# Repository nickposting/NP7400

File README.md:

# NP7400  

## Processor Card

### Docs
[g4pinout.pdf](/docs/g4pinout.pdf) contains the pinout of the connector used on
Power Mac G4 computers. Some important notes regarding the pinout:

* Pin assignments were determined by first sanding/filing down the processor
card (8 layers) from a 667MHz Digital Audio G4, and then using the card from
a 400MHz AGP Graphics G4, intact, albeit with the processor desoldered,
to verify that all the connections were correct.
* None of the cards involved in this process were dual-processor cards, so any
assignments unique to dual-processor systems, if any exist, have not been 
recorded.
* As written, the pin assignments are representative of how an MPC7450-series
MPU would be interfaced to the Power Mac motherboard -- for instance, only address
bits A4-A35 are present on the connector. Unlike earlier G4 processors, the 7450
features an extended 36-bit address bus, however, the four most significant bits
(A0-A3) are not used in Power Mac systems. Bearing in mind that PowerPC datasheet
conventions specify bit zero as the most-significant bit, a processor card design
featuring an earlier 7400/7410 MPU with a 32-bit address bus would need to have the
MPU's bit A31 connected to the pin labelled "A35" on the pinout, A30 connected to
"A34," and so on. The same applies to the DTI (Data Transaction Index) signals, of
which there are less on MPUs predating the 7450.

Regarding pins marked "special":
* Pins marked "R" are connected only to resistor straps, most of which go to ground.
I am still trying to understand the purpose of most of these. Some straps are
unpopulated on every board in my possession, whereas others vary between boards.
* SDA and SCL are connected only to the SPD I<sup>2</sup>C EEPROM on every board.
* Pins B2 and K30 are connected only to each other on every board. I assume this is
intended for the motherboard to sense whether or not the processor card is fully
seated.
* CKSTP# on the connector is directly connected to both CKSTP_IN# and CKSTP_OUT# on
the MPU.
* D63 is pulled to ground by a 1kΩ resistor on every board for some reason.
* The length of the SYSCLK track in particular is critical (tangentially, it appears
that on cards built for Power Macs with a 167MHz FSB, most track lengths become
tightly controlled).

## VRM

### Docs
[820-1152-A.pdf](/docs/820-1152-A.pdf) contains a poor schematic of the
original VRM board in the Power Mac G4 Cube, drawn only to verify whether or not
there was anything "unusual" about the OEM design (for all intents and purposes,
there isn't).
[np7400_VRM.pdf](/docs/np7400_VRM.pdf) contains the KiCad schematic of the
upgraded VRM board in PDF.

### Schematic and Board Layout
Schematic/layout files are provided as a complete KiCad project. As of the time
of this writing, schematic has been somewhat revised and does not reflect the
older revision of the layout included.

The newer schematic has not been thouroughly proofread. The older layout has not
been tested extensively and should not be used; there is considerable room for
improvement. Most planned changes are regarding optimization of routing, and ease
of assembly.

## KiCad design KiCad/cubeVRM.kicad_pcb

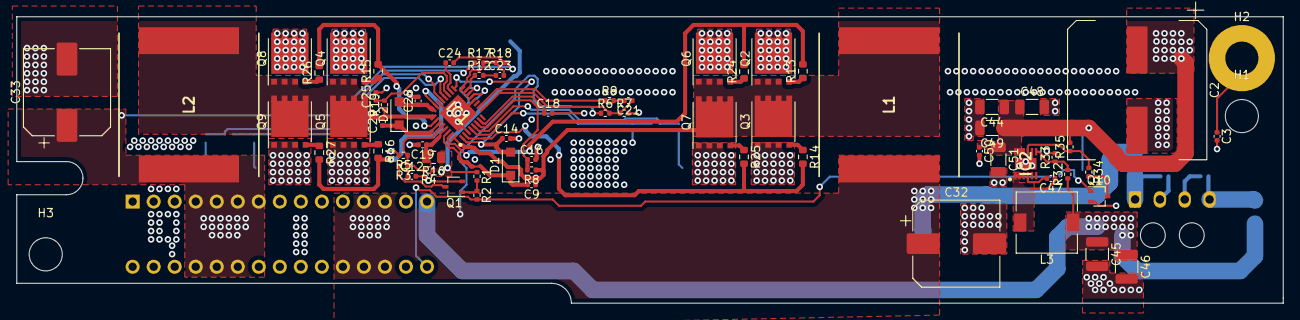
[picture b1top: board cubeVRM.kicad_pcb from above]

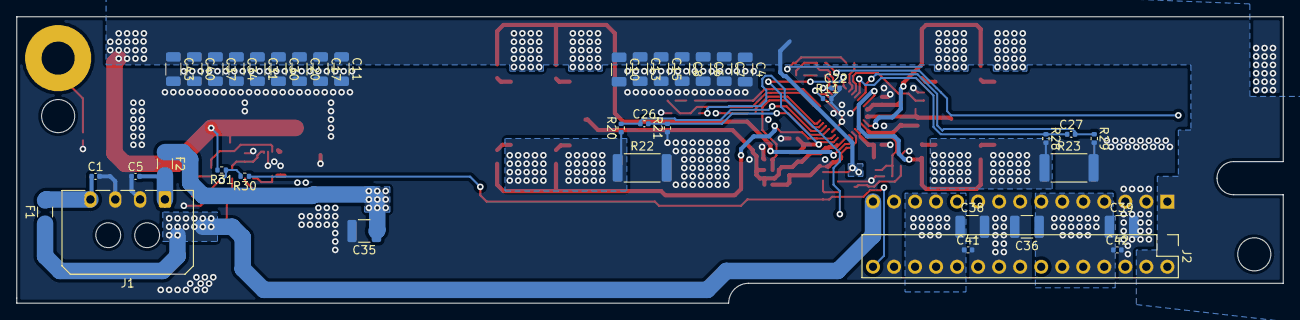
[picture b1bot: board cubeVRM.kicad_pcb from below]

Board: 4 copper layers, 153.0 x 34.6 mm, 110 parts (40 on the bottom side), 55 nets.

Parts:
C1, C5, C14, C28, C41, C42: 1uF; C_0402_1005Metric
C2: 680uF STANDARD; CP_Elec_16x17.5
C3: 1nF; C_0402_1005Metric
C4, C6, C7, C8, C10, C11, C13, C15, C17, C20, C30, C31, C34, C37, C40, C43: 2.2uF; C_1206_3216Metric
C9, C19, C22, C29: 0.47uF; C_0402_1005Metric
C12: 100pF; C_0402_1005Metric
C16, C25: 820pF; C_0402_1005Metric
C18, C24: 0.038uF; C_0402_1005Metric
C21, C23: 6800pF; C_0402_1005Metric
C26, C27: 1000pF; C_0402_1005Metric
C32, C33: 820uF; CP_Elec_10x10
C35, C36, C38, C39, C45, C46: 22uF; C_1210_3225Metric
C44, C48, C49, C51: 10uF; C_1206_3216Metric
C47, C50: 0.1uF; C_0402_1005Metric
D1, D2: D_Schottky; D_SOD-123F
F1, F2: 4A; Fuse_1206_3216Metric
H1, H3: MountingHole_NP; MountingHole_4mm
H2: MountingHole_Pad; MountingHole_4mm_Pad
IC1: LM25119QPSQ_NOPB; QFN50P500X500X80-33N
IC2: LMR51450FNDRRR; SON50P300X300X80-13N-D
J1: Conn_01x04; Molex_Micro-Fit_3.0_43650-0400_1x04_P3.00mm_Horizontal
J2: Conn_02x15_Odd_Even; PinHeader_2x15_P2.54mm_Vertical
L1: 8.2uH; INDPM173169X700N
L2: 5.6uH; INDPM173169X700N
L3: 6.8uH; L_7.3x7.3_H4.5
Q1, Q10: 2N3904; SOT-323_SC-70
Q2, Q3, Q4, Q5, Q6, Q7, Q8, Q9: Q_NMOS_DGS; VSONP-8-1EP_5x6_P1.27mm
R1, R31, R32, R35: 100k; R_0402_1005Metric
R2, R30, R34: 100R; R_0402_1005Metric
R3: 47R; R_0402_1005Metric
R4: 52.3k; R_0402_1005Metric
R5: 3k; R_0402_1005Metric
R6: 5.76k; R_0402_1005Metric
R7: 1.1k; R_0402_1005Metric
R8: 124k; R_0402_1005Metric
R9: 30k; R_0402_1005Metric
R10: 3.9R; R_0805_2012Metric
R11: 24.9k; R_0402_1005Metric
R12: 20.5k; R_0402_1005Metric
R13, R14, R15, R16, R24, R25, R26, R27: 10R; R_0603_1608Metric
R17: 3.92k; R_0402_1005Metric
R18: 1.24k; R_0402_1005Metric
R19: 84.5k; R_0402_1005Metric
R20, R21, R28, R29: 10R; R_0402_1005Metric
R22, R23: 0R005; R_2512_6332Metric
R33: 7.15k; R_0402_1005Metric

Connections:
28VDC: C2.1, C4.1, C6.1, C7.1, C8.1, C10.1, C11.1, C13.1, C15.1, C17.1, C20.1, C30.1, C31.1, C34.1, C37.1, C40.1, C43.1, C44.1, C48.1, C49.1, C50.1, C51.1, IC2.10, IC2.11, IC2.12, J2.1, J2.2, J2.4, Q2.3, Q4.3, Q6.3, Q8.3, R1.1, R4.1, R10.1, R31.2, R35.2
+3V3: C33.1, C36.1, C39.1, C42.1, J2.7, J2.8, J2.9, J2.10, J2.11, J2.12, J2.13, L2.2, R17.1
+5V: C32.1, C35.1, C38.1, C41.1, F2.1, J2.22, J2.23, J2.24, J2.25, J2.26, L1.2, R6.1
+12V: C45.1, C46.1, F1.1, J2.29, L3.1, R32.1
GND: C1.2, C2.2, C3.2, C4.2, C5.1, C6.2, C7.2, C8.2, C10.2, C11.2, C12.2, C13.2, C14.2, C15.2, C16.2, C17.2, C18.2, C19.2, C20.2, C22.2, C24.2, C25.2, C28.2, C30.2, C31.2, C32.2, C33.2, C34.2, C35.2, C36.2, C37.2, C38.2, C39.2, C40.2, C41.2, C42.2, C43.2, C44.2, C45.2, C46.2, C48.2, C49.2, C50.2, C51.2, IC1.3, IC1.12, IC1.22, IC1.33, IC2.8, IC2.13, J1.2, J1.3, J2.3, J2.5, J2.6, J2.14, J2.15, J2.16, J2.17, J2.18, J2.19, J2.20, J2.21, J2.27, J2.28, Q1.1, Q10.1, R5.2, R7.2, R11.2, R18.2, R21.1, R22.2, R23.2, R29.2, R33.2
HB1: C9.2, D1.1, IC1.30
HB2: C29.1, D2.1, IC1.27
unnamed: C1.1, F1.2, J1.4
unnamed: C3.1, H2.1
unnamed: C5.2, F2.2, J1.1
unnamed: C9.1, IC1.32, L1.1, Q2.1, Q3.3, Q6.1, Q7.3, R8.1
unnamed: C12.1, IC1.28, R3.1, R4.2, R5.1
unnamed: C14.1, D1.2, IC1.1, IC1.17
unnamed: C16.1, IC1.6, R8.2
unnamed: C18.1, IC1.7
unnamed: C19.1, IC1.29, R10.2
unnamed: C21.1, IC1.9, R6.2, R7.1
unnamed: C21.2, R9.2
unnamed: C22.1, IC1.14
unnamed: C23.1, R12.2
unnamed: C23.2, IC1.16, R17.2, R18.1
unnamed: C24.1, IC1.18
unnamed: C25.1, IC1.19, R19.2
unnamed: C26.1, IC1.5, R20.2
unnamed: C26.2, IC1.4, R21.2
unnamed: C27.1, IC1.20, R28.1
unnamed: C27.2, IC1.21, R29.1
unnamed: C28.1, D2.2, IC1.24
unnamed: C29.2, IC1.25, L2.1, Q4.1, Q5.3, Q8.1, Q9.3, R19.1
unnamed: C47.1, IC2.1, IC2.2, IC2.3, L3.2
unnamed: C47.2, IC2.4
unnamed: IC1.2, R14.2, R25.2
unnamed: IC1.10, R9.1
unnamed: IC1.13, R11.1
unnamed: IC1.15, R12.1
unnamed: IC1.23, R16.2, R27.2
unnamed: IC1.26, R15.2, R26.2
unnamed: IC1.31, R13.2, R24.2
unnamed: IC2.7, R32.2, R33.1
unnamed: IC2.9, R34.1, R35.1
unnamed: Q1.2, R1.2, R2.1
unnamed: Q1.3, R3.2
unnamed: Q2.2, R13.1
unnamed: Q3.1, Q7.1, R20.1, R22.1
unnamed: Q3.2, R14.1
unnamed: Q4.2, R15.1
unnamed: Q5.1, Q9.1, R23.1, R28.2
unnamed: Q5.2, R16.1
unnamed: Q6.2, R24.1
unnamed: Q7.2, R25.1
unnamed: Q8.2, R26.1
unnamed: Q9.2, R27.1
unnamed: Q10.2, R30.2, R31.1
unnamed: Q10.3, R34.2
STANDBY: J2.30, R2.2, R30.1

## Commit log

2023-09-29 Add schematics, layout files
    Revising schematic, does not match layout (rev1) or netlist yet. Strongly recommend against using rev1 board layout; still in dire need of optimization
2023-09-30 Move VRM design files, add processor card pinout and notes
